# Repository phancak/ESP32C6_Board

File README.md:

# ESP32-C6 Expansion Board

## Overview

This project features a modular expansion board based on the **ESP32-C6** microcontroller, designed to showcase advanced wireless connectivity and interface flexibility for proof-of-concept embedded systems. The board includes **Wi-Fi 6**, **Bluetooth 5**, and **802.15.4 (Thread/Zigbee)** support, making it suitable for modern IoT applications. In addition to its wireless capabilities, the board exposes key communication interfaces like **QSPI**, **SPI**, **I2C**, and **UART**, enabling it to serve as a powerful, plug-and-play module in larger prototype systems.

## Features

- **ESP32-C6 MCU** – RISC-V single-core processor with Wi-Fi 6, BLE 5, Thread, and Zigbee support
- **QSPI Interface** – For high-speed flash memory or display integration
- **SPI, I2C, UART** – Standard communication protocols for versatile interfacing
- **Low Power Operation** – Ideal for battery-powered and energy-conscious applications
- **Modular Design** – Created for reuse across multiple proof-of-concept hardware projects

## Applications

- **IoT Prototyping** – Wireless communication for smart sensors and devices
- **Home Automation** – Thread/Zigbee-enabled devices with cloud connectivity
- **Industrial Monitoring** – Robust wireless links in noisy environments
- **Education & Research** – Hands-on embedded systems development

## Getting Started

### Hardware Requirements

- ESP32-C6 Expansion Board
- Host MCU or baseboard (if applicable)
- USB-C or serial programmer (if needed)
- 3.3V power supply

### Software Requirements

- [ESP-IDF](https://docs.espressif.com/projects/esp-idf/en/latest/esp32c6/index.html) – Espressif's official development framework
- [esptool.py](https://github.com/espressif/esptool) – Flashing utility
- Serial terminal (e.g., `minicom`, `screen`, or [CoolTerm](https://freeware.the-meiers.org/))

## Setup & Usage

1. **Power the Board** – Supply 3.3V through header or onboard regulator.
2. **Connect to PC** – Use a USB-to-serial adapter if required.
3. **Flash Firmware** – Use `esptool.py` or ESP-IDF to upload your application.
4. **Interface with Peripherals** – Connect SPI/I2C/UART/QSPI devices as needed.
5. **Run Application** – Test wireless or peripheral functionality in your project.

## Schematic

You can view the schematic [here](ESP32C6_Board_Schematics.pdf).

## Future Enhancements

- 🔹 **Thread/Zigbee Demos** – Example apps using 802.15.4 stack
- 🔹 **External Flash/Display Support** – Over QSPI
- 🔹 **Power Optimization Modes** – Advanced sleep and wake-up configurations
- 🔹 **Plug-in Board Compatibility** – For stacking with other expansions

## License

This project is open-source under the **MIT License**.

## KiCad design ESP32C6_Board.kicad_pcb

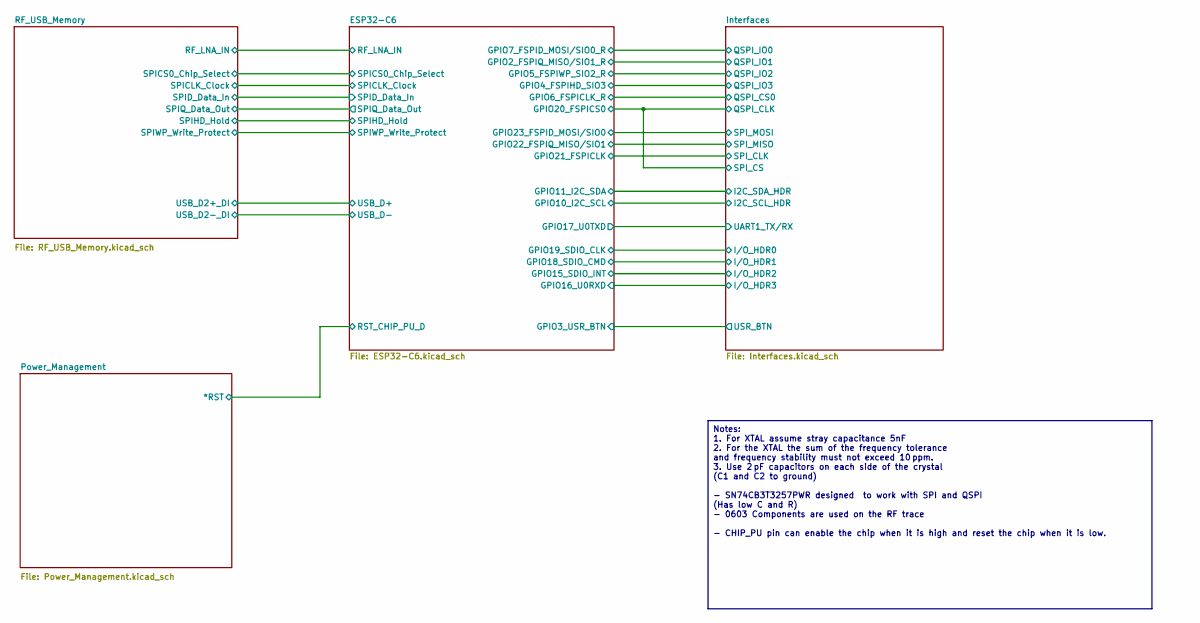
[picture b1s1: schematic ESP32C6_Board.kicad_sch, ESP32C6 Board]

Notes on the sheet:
Notes: 1. For XTAL assume stray capacitance 5nF 2. For the XTAL the sum of the frequency tolerance and frequency stability must not exceed 10 ppm. 3. Use 2 pF capacitors on each side of the crystal (C1 and C2 to ground) - SN74CB3T3257PWR designed to work with SPI and QSPI (Has low C and R) - 0603 C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

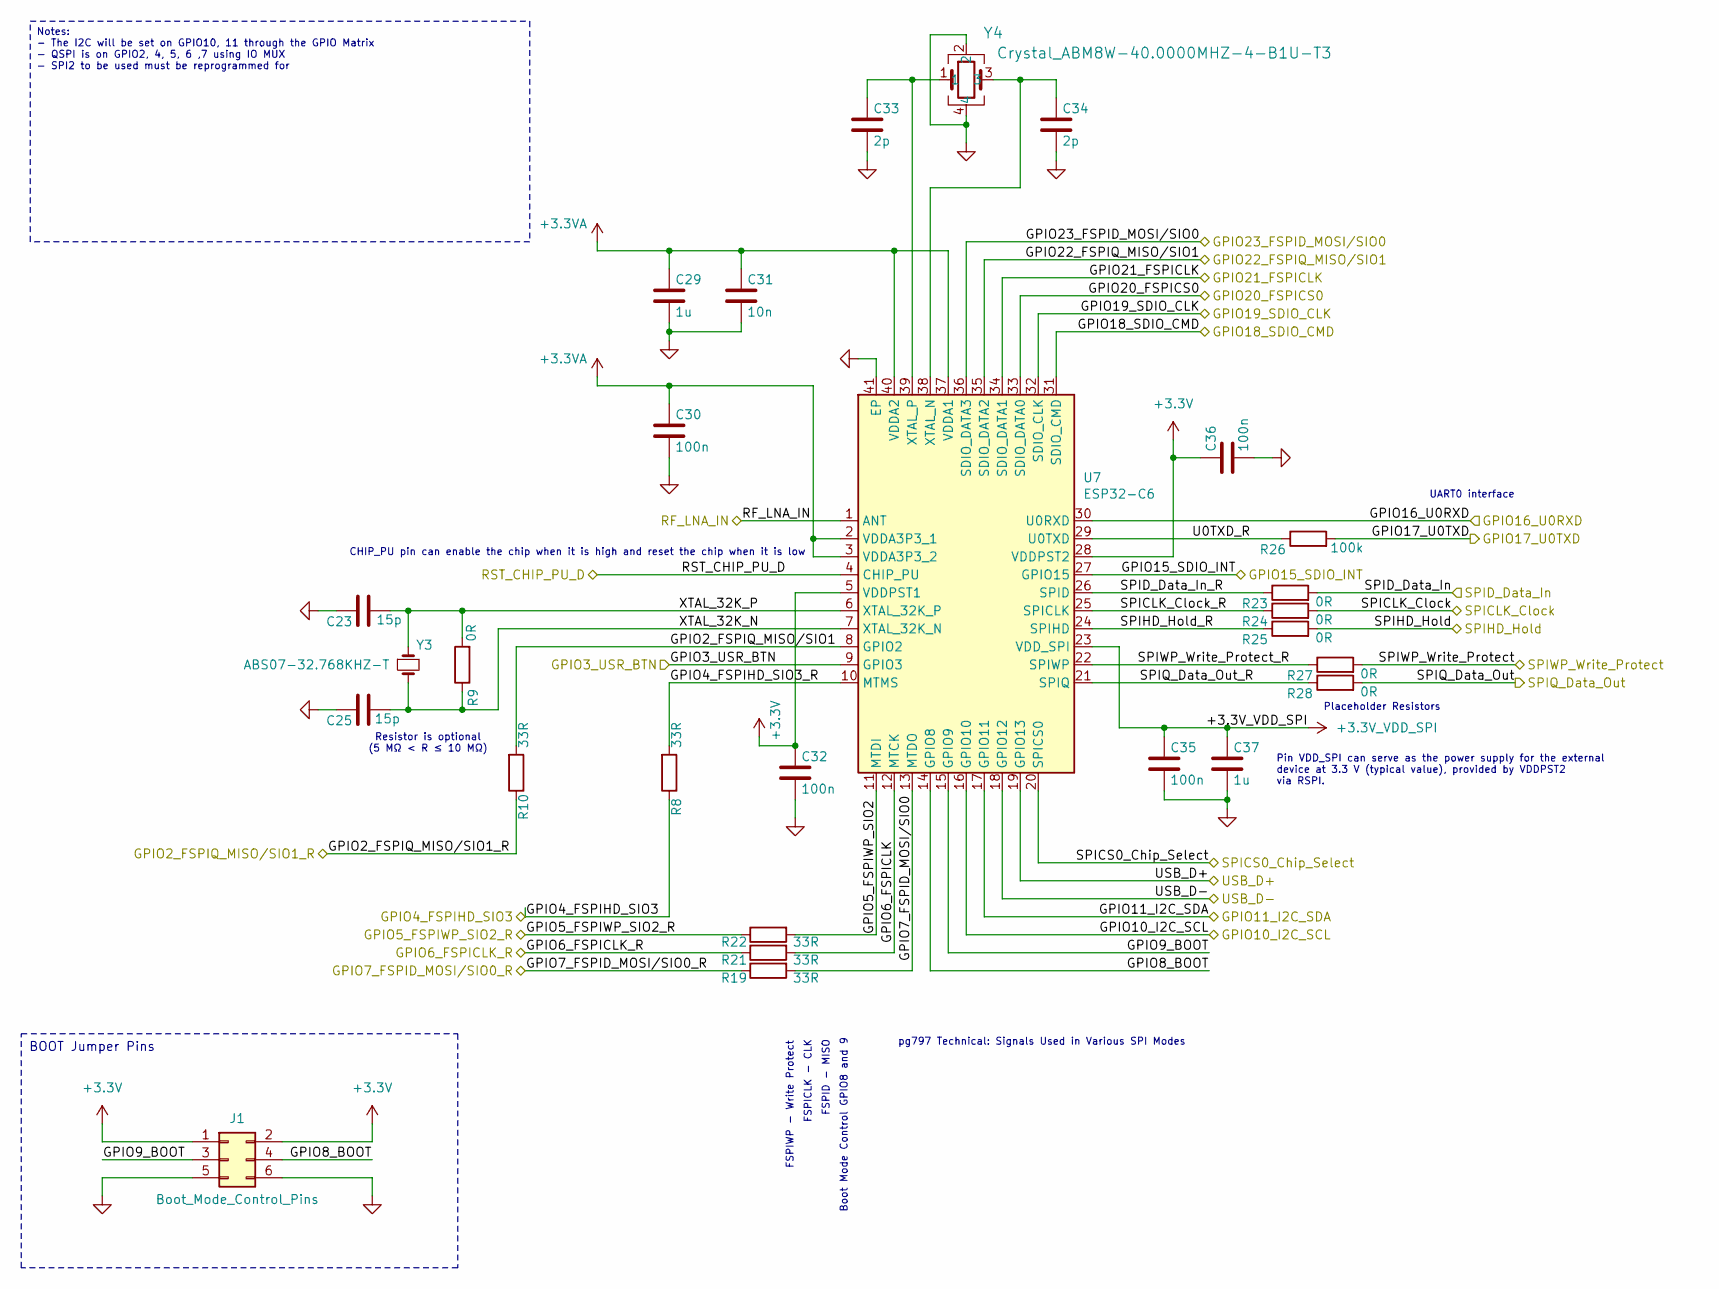
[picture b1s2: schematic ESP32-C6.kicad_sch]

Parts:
C23, C25: 15p; C_0805_2012Metric
C29, C37: 1u; C_0805_2012Metric
C30, C32, C35, C36: 100n; C_0805_2012Metric
C31: 10n; C_0805_2012Metric
C33, C34: 2p; C_0805_2012Metric
J1: Boot_Mode_Control_Pins; PinHeader_2x03_P2.54mm_Vertical
R8, R10, R19, R21, R22: 33R; R_0805_2012Metric
R9, R23, R24, R25, R27, R28: 0R; R_0805_2012Metric
R26: 100k; R_0805_2012Metric
U7: ESP32-C6; ESP32C6_QFN40P500X500X90-41N-D; Mouser Part Number 356-ESP32-C6
Y3: ABS07-32.768KHZ-T; Crystal_ABS07
Y4: Crystal_ABM8W-40.0000MHZ-4-B1U-T3; CRYSTAL4_ABM10W-40.0000MHZ-8-B1U-T3_ABR

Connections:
+3.3V: C32.1, C36.1, J1.1, J1.2, U7.5 (VDDPST1), U7.28 (VDDPST2); also elsewhere on the board
+3.3VA: C29.1, C30.1, C31.1, U7.2 (VDDA3P3_1), U7.3 (VDDA3P3_2), U7.37 (VDDA1), U7.40 (VDDA2); also elsewhere on the board
+3.3V_VDD_SPI: C35.1, C37.1, U7.23 (VDD_SPI); also elsewhere on the board
/ESP32-C6/GPIO2_FSPIQ_MISO/SIO1: R10.2, U7.8 (GPIO2)
/ESP32-C6/GPIO2_FSPIQ_MISO/SIO1_R: R10.1; also elsewhere on the board
/ESP32-C6/GPIO3_USR_BTN: U7.9 (GPIO3); also elsewhere on the board
/ESP32-C6/GPIO4_FSPIHD_SIO3: R8.1; also elsewhere on the board
/ESP32-C6/GPIO4_FSPIHD_SIO3_R: R8.2, U7.10 (MTMS)
/ESP32-C6/GPIO5_FSPIWP_SIO2: R22.2, U7.11 (MTDI)
/ESP32-C6/GPIO5_FSPIWP_SIO2_R: R22.1; also elsewhere on the board
/ESP32-C6/GPIO6_FSPICLK: R21.2, U7.12 (MTCK)
/ESP32-C6/GPIO6_FSPICLK_R: R21.1; also elsewhere on the board
/ESP32-C6/GPIO7_FSPID_MOSI/SIO0: R19.2, U7.13 (MTDO)
/ESP32-C6/GPIO7_FSPID_MOSI/SIO0_R: R19.1; also elsewhere on the board
/ESP32-C6/GPIO8_BOOT: J1.4, U7.14 (GPIO8)
/ESP32-C6/GPIO9_BOOT: J1.3, U7.15 (GPIO9)
/ESP32-C6/GPIO10_I2C_SCL: U7.16 (GPIO10); also elsewhere on the board
/ESP32-C6/GPIO11_I2C_SDA: U7.17 (GPIO11); also elsewhere on the board
/ESP32-C6/GPIO15_SDIO_INT: U7.27 (GPIO15); also elsewhere on the board
/ESP32-C6/GPIO16_U0RXD: U7.30 (U0RXD); also elsewhere on the board
/ESP32-C6/GPIO17_U0TXD: R26.2; also elsewhere on the board
/ESP32-C6/GPIO18_SDIO_CMD: U7.31 (SDIO_CMD); also elsewhere on the board
/ESP32-C6/GPIO19_SDIO_CLK: U7.32 (SDIO_CLK); also elsewhere on the board
/ESP32-C6/GPIO20_FSPICS0: U7.33 (SDIO_DATA0); also elsewhere on the board
/ESP32-C6/GPIO21_FSPICLK: U7.34 (SDIO_DATA1); also elsewhere on the board
/ESP32-C6/GPIO22_FSPIQ_MISO/SIO1: U7.35 (SDIO_DATA2); also elsewhere on the board
/ESP32-C6/GPIO23_FSPID_MOSI/SIO0: U7.36 (SDIO_DATA3); also elsewhere on the board
/ESP32-C6/RF_LNA_IN: U7.1 (ANT); also elsewhere on the board
/ESP32-C6/RST_CHIP_PU_D: U7.4 (CHIP_PU); also elsewhere on the board
/ESP32-C6/SPICLK_Clock: R24.2; also elsewhere on the board
/ESP32-C6/SPICLK_Clock_R: R24.1, U7.25 (SPICLK)
/ESP32-C6/SPICS0_Chip_Select: U7.20 (SPICS0); also elsewhere on the board
/ESP32-C6/SPID_Data_In: R23.2; also elsewhere on the board
/ESP32-C6/SPID_Data_In_R: R23.1, U7.26 (SPID)
/ESP32-C6/SPIHD_Hold: R25.2; also elsewhere on the board
/ESP32-C6/SPIHD_Hold_R: R25.1, U7.24 (SPIHD)
/ESP32-C6/SPIQ_Data_Out: R28.2; also elsewhere on the board
/ESP32-C6/SPIQ_Data_Out_R: R28.1, U7.21 (SPIQ)
/ESP32-C6/SPIWP_Write_Protect: R27.2; also elsewhere on the board
/ESP32-C6/SPIWP_Write_Protect_R: R27.1, U7.22 (SPIWP)
/ESP32-C6/U0TXD_R: R26.1, U7.29 (U0TXD)
/ESP32-C6/USB_D+: U7.19 (GPIO13); also elsewhere on the board
/ESP32-C6/USB_D-: U7.18 (GPIO12); also elsewhere on the board
/ESP32-C6/XTAL_32K_N: C25.1, R9.1, U7.7 (XTAL_32K_N), Y3.2
/ESP32-C6/XTAL_32K_P: C23.1, R9.2, U7.6 (XTAL_32K_P), Y3.1
GND: C23.2, C25.2, C29.2, C30.2, C31.2, C32.2, C33.2, C34.2, C35.2, C36.2, C37.2, J1.5, J1.6, U7.41 (EP), Y4.2, Y4.4; also elsewhere on the board
unnamed: C34.1, U7.38 (XTAL_N), Y4.3
unnamed: C33.1, U7.39 (XTAL_P), Y4.1

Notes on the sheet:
BOOT Jumper Pins
Notes: - The I2C will be set on GPIO10, 11 through the GPIO Matrix - QSPI is on GPIO2, 4, 5, 6 ,7 using IO MUX - SPI2 to be used must be reprogrammed for
Resistor is optional (5 MΩ < R ≤ 10 MΩ)
FSPIWP - Write Protect
FSPID - MISO
FSPICLK - CLK
UART0 interface
Placeholder Resistors
Boot Mode Control GPIO8 and 9
Pin VDD_SPI can serve as the power supply for the external device at 3.3 V (typical value), provided by VDDPST2 via RSPI.
CHIP_PU pin can enable the chip when it is high and reset the chip when it is low
pg797 Technical: Signals Used in Various SPI Modes

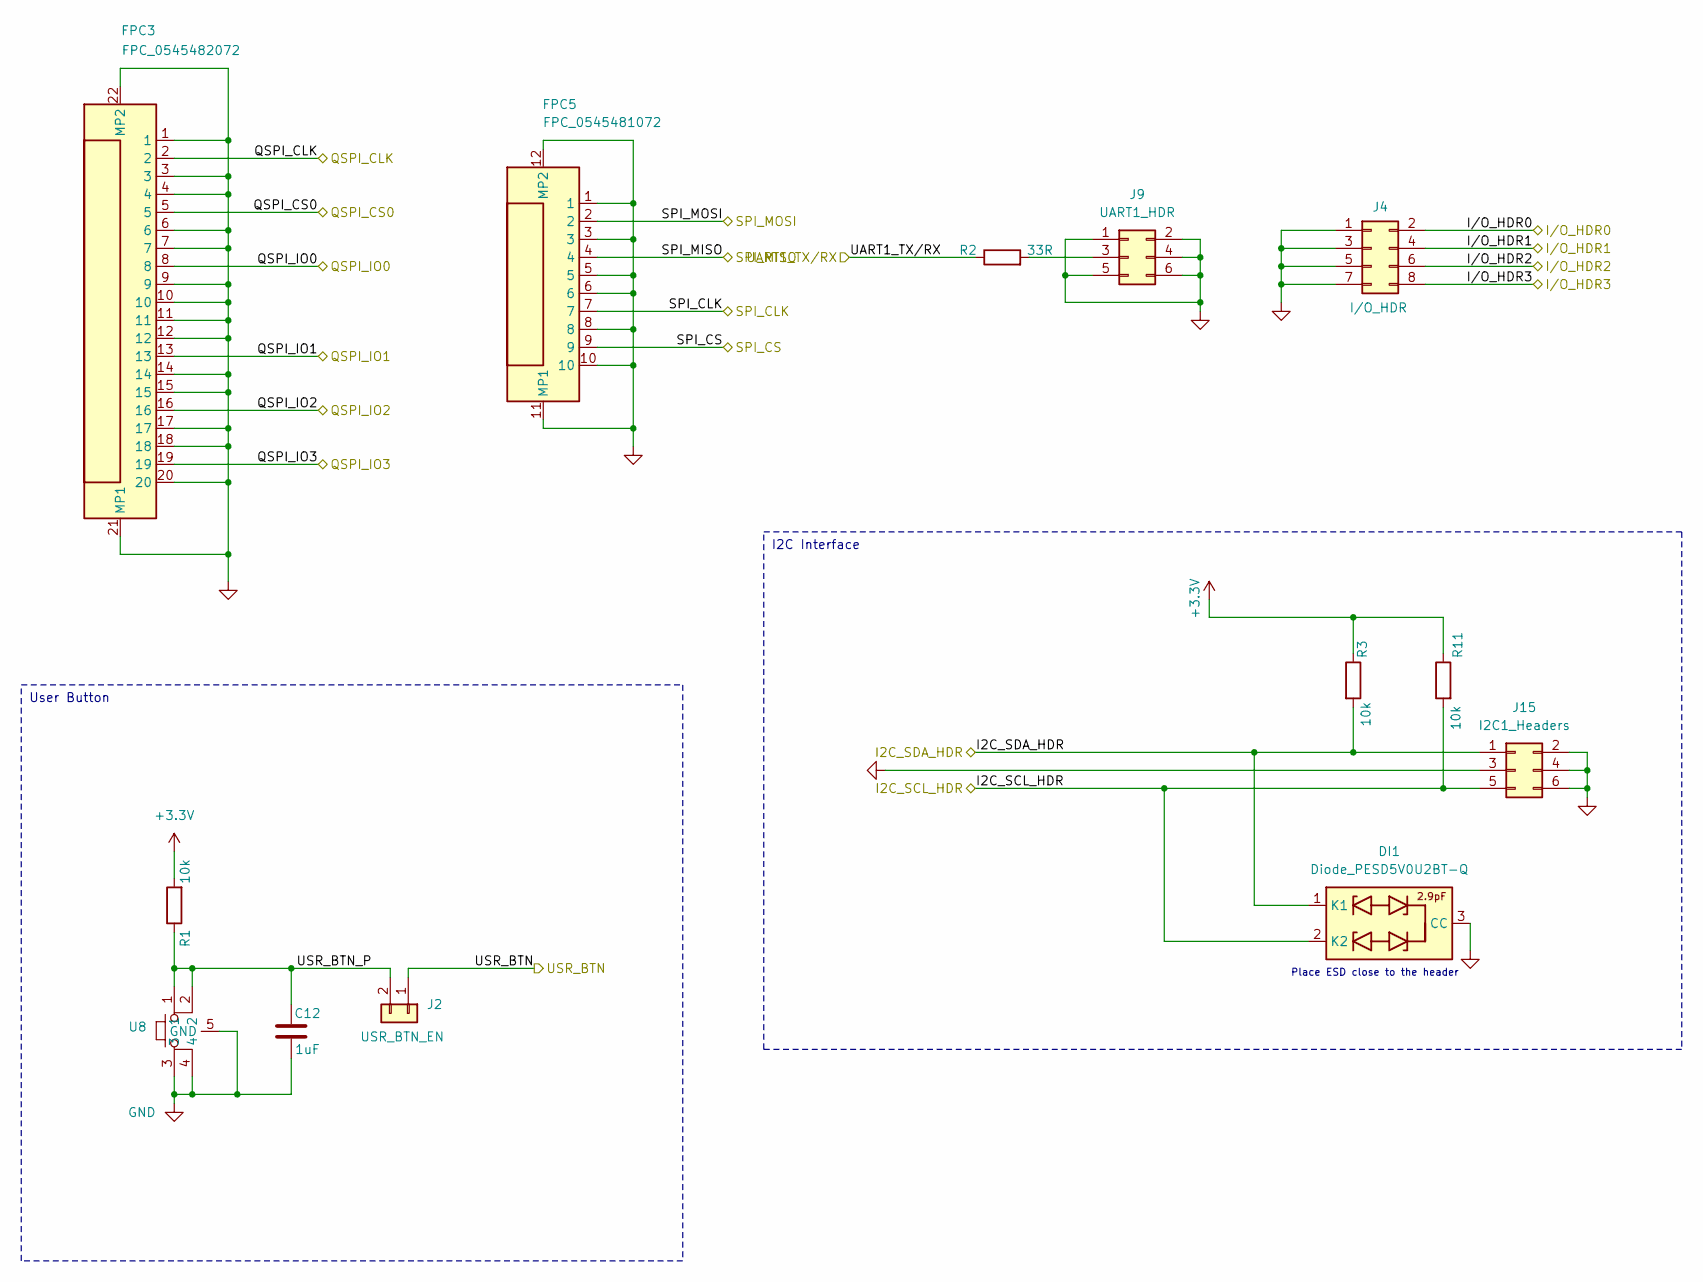
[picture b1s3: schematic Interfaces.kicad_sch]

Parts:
C12: 1uF; C_0805_2012Metric
DI1: Diode_PESD5V0U2BT-Q; SOT-23; Manufacturer_Part_Number BZX84C6V2-7-F; Mouser Part Number 621-BZX84C6V2-F
FPC3: FPC_0545482072; Manufacturer_Part_Number 0545481072
FPC5: FPC_0545481072; Manufacturer_Part_Number 0545481072
J2: USR_BTN_EN; PinHeader_1x02_P2.54mm_Vertical
J4: I/O_HDR; PinHeader_2x04_P2.54mm_Horizontal
J9: UART1_HDR; PinHeader_2x03_P2.54mm_Horizontal_Court
J15: I2C1_Headers; PinHeader_2x03_P2.54mm_Horizontal_Court
R1, R3, R11: 10k; R_0805_2012Metric
R2: 33R; R_0805_2012Metric
U8: Button_KMR231GLFS

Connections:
+3.3V: R1.2, R3.1, R11.1; also elsewhere on the board
/ESP32-C6/GPIO2_FSPIQ_MISO/SIO1_R: FPC3.13; also elsewhere on the board
/ESP32-C6/GPIO3_USR_BTN: J2.1; also elsewhere on the board
/ESP32-C6/GPIO4_FSPIHD_SIO3: FPC3.19; also elsewhere on the board
/ESP32-C6/GPIO5_FSPIWP_SIO2_R: FPC3.16; also elsewhere on the board
/ESP32-C6/GPIO6_FSPICLK_R: FPC3.5; also elsewhere on the board
/ESP32-C6/GPIO7_FSPID_MOSI/SIO0_R: FPC3.8; also elsewhere on the board
/ESP32-C6/GPIO10_I2C_SCL: DI1.2 (K2), J15.5, R11.2; also elsewhere on the board
/ESP32-C6/GPIO11_I2C_SDA: DI1.1 (K1), J15.1, R3.2; also elsewhere on the board
/ESP32-C6/GPIO15_SDIO_INT: J4.6; also elsewhere on the board
/ESP32-C6/GPIO16_U0RXD: J4.8; also elsewhere on the board
/ESP32-C6/GPIO17_U0TXD: R2.1; also elsewhere on the board
/ESP32-C6/GPIO18_SDIO_CMD: J4.4; also elsewhere on the board
/ESP32-C6/GPIO19_SDIO_CLK: J4.2; also elsewhere on the board
/ESP32-C6/GPIO20_FSPICS0: FPC3.2, FPC5.9; also elsewhere on the board
/ESP32-C6/GPIO21_FSPICLK: FPC5.7; also elsewhere on the board
/ESP32-C6/GPIO22_FSPIQ_MISO/SIO1: FPC5.4; also elsewhere on the board
/ESP32-C6/GPIO23_FSPID_MOSI/SIO0: FPC5.2; also elsewhere on the board
/Interfaces/USR_BTN_P: C12.2, J2.2, R1.1, U8.1, U8.2
GND: C12.1, DI1.3 (CC), FPC3.1, FPC3.3, FPC3.4, FPC3.6, FPC3.7, FPC3.9, FPC3.10, FPC3.11, FPC3.12, FPC3.14, FPC3.15, FPC3.17, FPC3.18, FPC3.20, FPC3.21 (MP1), FPC3.22 (MP2), FPC5.1, FPC5.3, FPC5.5, FPC5.6, FPC5.8, FPC5.10, FPC5.11 (MP1), FPC5.12 (MP2), J4.1, J4.3, J4.5, J4.7, J9.1, J9.2, J9.4, J9.5, J9.6, J15.2, J15.3, J15.4, J15.6, U8.3, U8.4, U8.5 (GND); also elsewhere on the board
unnamed: J9.3, R2.2

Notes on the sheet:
User Button
I2C Interface
Place ESD close to the header

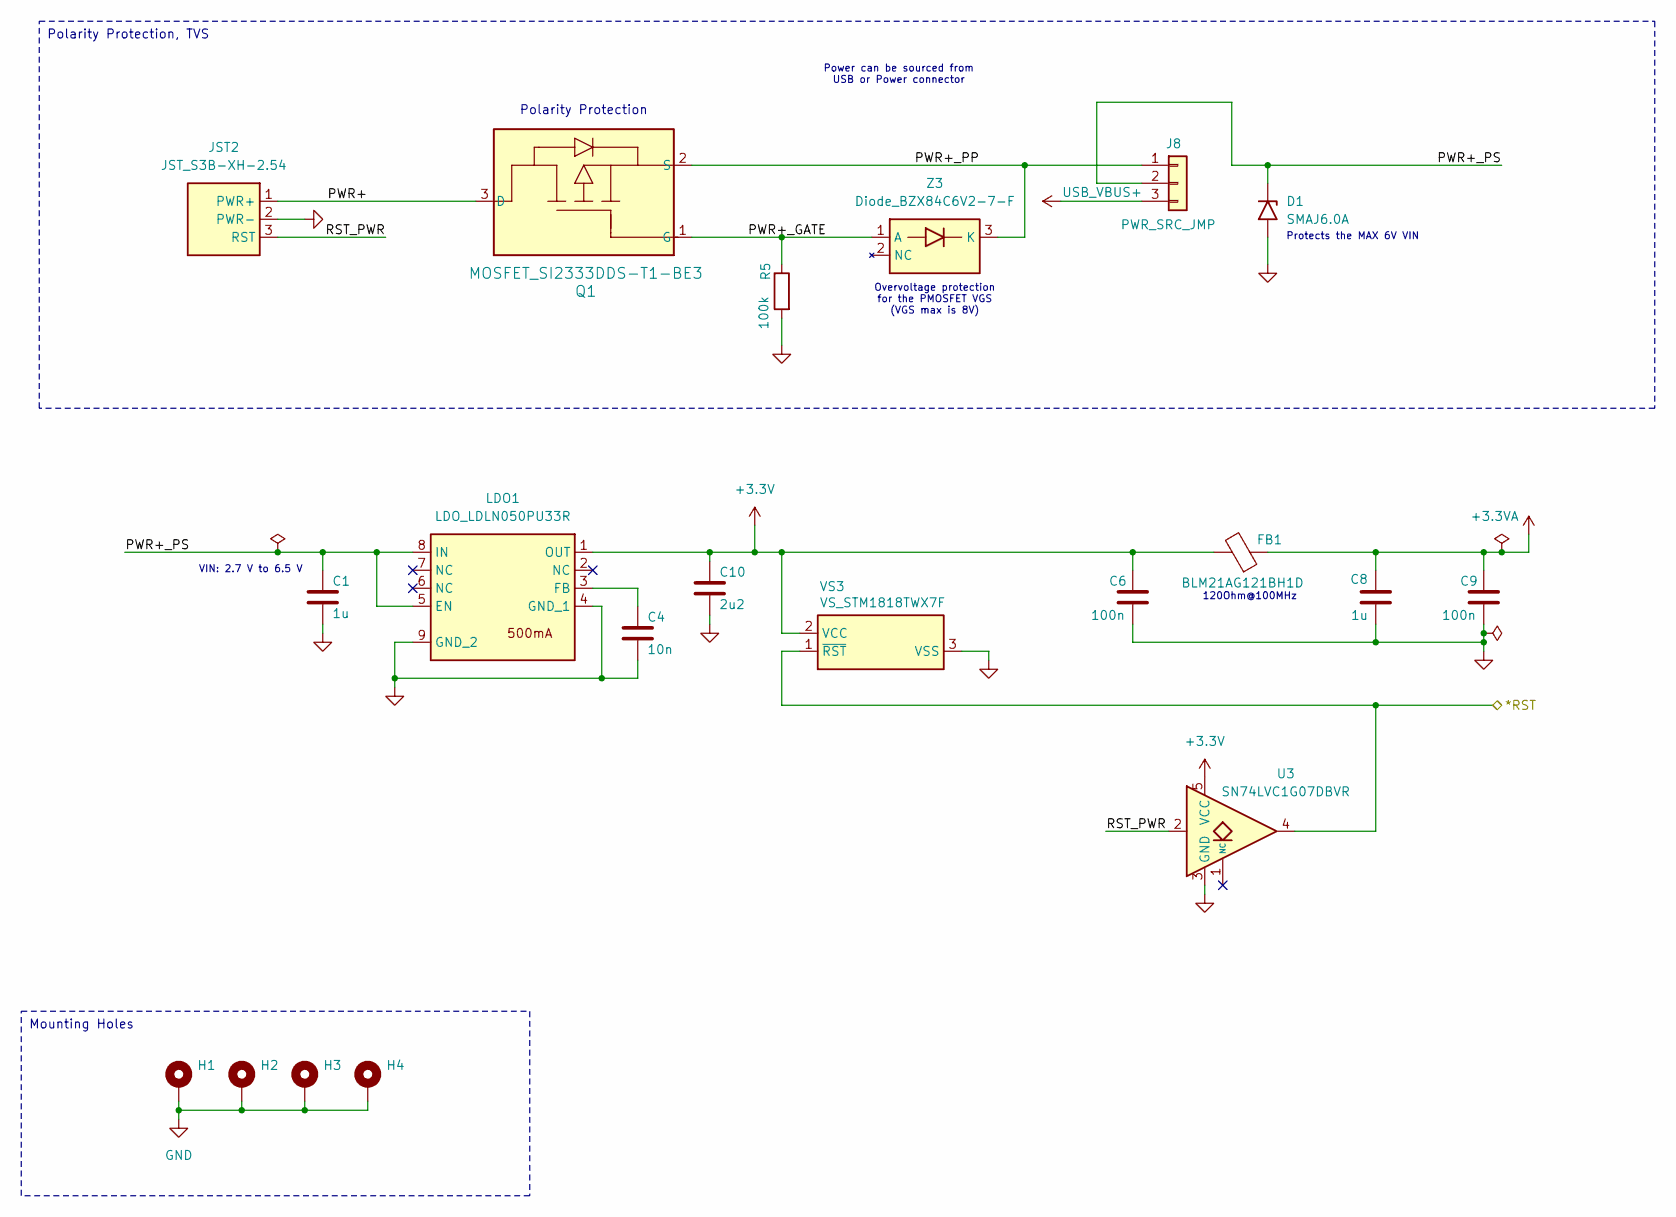
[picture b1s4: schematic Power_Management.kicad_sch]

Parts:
C1, C8: 1u; C_0805_2012Metric
C4: 10n; C_0805_2012Metric
C6, C9: 100n; C_0805_2012Metric
C10: 2u2; C_0805_2012Metric
D1: SMAJ6.0A; DO-214AC-2
FB1: BLM21AG121BH1D; C_0805_2012Metric
H1, H2, H3, H4: MountingHole_Pad; MountingHole_3.2mm_M3_Pad
J8: PWR_SRC_JMP; PinHeader_1x03_P2.54mm_Vertical
JST2: JST_S3B-XH-2.54; JST_S3B-XH-SHDRRA3W64P0X250_1X3_990X1150X610P; Mouser Part Number 306-S3BXHA1LFSN
LDO1: LDO_LDLN050PU33R; DFN-8-1EP_3x3mm_P0.65mm_EP1.7x2.05mm; Manufacturer_Part_Number LD39200DPUR; Mouser Part Number 511-LD39200DPUR
Q1: MOSFET_SI2333DDS-T1-BE3; MOSFET_ SI2333DDS_SOT_DS-T1-BE3_VIS
R5: 100k; R_0805_2012Metric
U3: SN74LVC1G07DBVR; SOT-23-5
VS3: VS_STM1818TWX7F; SOT-23-3_SOT103P237X112-3N; Mouser Part Number 511-STM1813LWX7F
Z3: Diode_BZX84C6V2-7-F; Diode_BZX84C6V2_SOT96P240X110-3N; Manufacturer_Part_Number BZX84C6V2-7-F; Mouser Part Number 621-BZX84C6V2-F

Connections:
+3.3V: C6.1, C10.1, FB1.2, LDO1.1 (OUT), U3.5 (VCC), VS3.2 (VCC); also elsewhere on the board
+3.3VA: C8.1, C9.1, FB1.1; also elsewhere on the board
/ESP32-C6/RST_CHIP_PU_D: U3.4, VS3.1 (~RST); also elsewhere on the board
/Power_Management/PWR+: JST2.1 (PWR+), Q1.3 (D)
/Power_Management/PWR+_GATE: Q1.1 (G), R5.1, Z3.1 (A)
/Power_Management/PWR+_PP: J8.1, Q1.2 (S), Z3.3 (K)
/Power_Management/PWR+_PS: C1.1, D1.1 (K), J8.2, LDO1.5 (EN), LDO1.8 (IN)
/Power_Management/RST_PWR: JST2.3 (RST), U3.2
GND: C1.2, C4.2, C6.2, C8.2, C9.2, C10.2, D1.2 (A), H1.1, H2.1, H3.1, H4.1, JST2.2 (PWR-), LDO1.4 (GND_1), LDO1.9 (GND_2), R5.2, U3.3 (GND), VS3.3 (VSS); also elsewhere on the board
unnamed: C4.1, LDO1.3 (FB)
USB_VBUS+: J8.3; also elsewhere on the board

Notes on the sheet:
Mounting Holes
Polarity Protection, TVS
Power can be sourced from USB or Power connector
120Ohm@100MHz
VIN: 2.7 V to 6.5 V
Overvoltage protection for the PMOSFET VGS (VGS max is 8V)
Protects the MAX 6V VIN
Polarity Protection

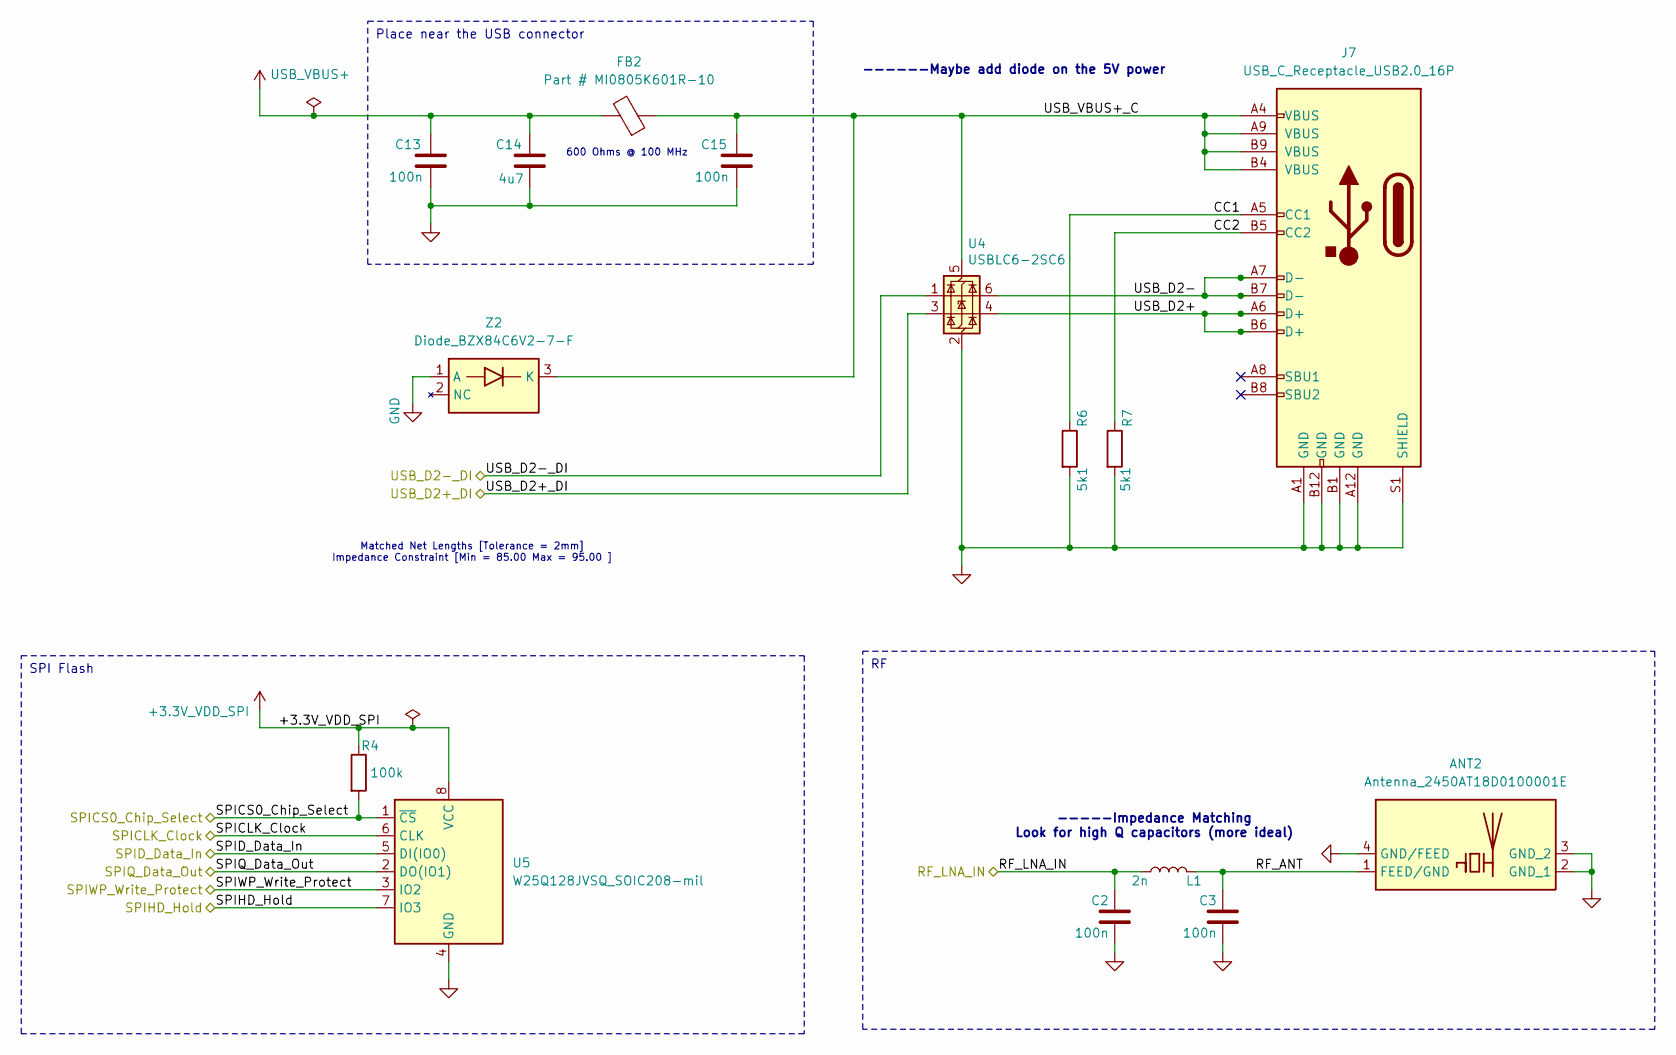
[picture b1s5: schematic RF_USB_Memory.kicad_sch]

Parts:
ANT2: Antenna_2450AT18D0100001E; Mouser Part Number 609-2450AT18D0100001
C2, C3: 100n; C_0603_1608Metric
C13, C15: 100n; C_0805_2012Metric
C14: 4u7; C_0805_2012Metric
FB2: Part # MI0805K601R-10; C_0805_2012Metric
J7: USB_C_Receptacle_USB2.0_16P; USB_C_Receptacle_HRO_TYPE-C-31-M-12
L1: 2n; L_0603_1608Metric
R4: 100k; R_0805_2012Metric
R6, R7: 5k1; R_0805_2012Metric
U4: USBLC6-2SC6; SOT-23-6
U5: W25Q128JVSQ_SOIC208-mil; SOIC-8_5.23x5.23mm_P1.27mm
Z2: Diode_BZX84C6V2-7-F; Diode_BZX84C6V2_SOT96P240X110-3N; Manufacturer_Part_Number BZX84C6V2-7-F; Mouser Part Number 621-BZX84C6V2-F

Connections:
+3.3V_VDD_SPI: R4.1, U5.8 (VCC); also elsewhere on the board
/ESP32-C6/RF_LNA_IN: C2.1, L1.2; also elsewhere on the board
/ESP32-C6/SPICLK_Clock: U5.6 (CLK); also elsewhere on the board
/ESP32-C6/SPICS0_Chip_Select: R4.2, U5.1 (~CS); also elsewhere on the board
/ESP32-C6/SPID_Data_In: U5.5 (DI(IO0)); also elsewhere on the board
/ESP32-C6/SPIHD_Hold: U5.7 (IO3); also elsewhere on the board
/ESP32-C6/SPIQ_Data_Out: U5.2 (DO(IO1)); also elsewhere on the board
/ESP32-C6/SPIWP_Write_Protect: U5.3 (IO2); also elsewhere on the board
/ESP32-C6/USB_D+: U4.3 (I/O2); also elsewhere on the board
/ESP32-C6/USB_D-: U4.1 (I/O1); also elsewhere on the board
/RF_USB_Memory/CC1: J7.A5 (CC1), R6.1
/RF_USB_Memory/CC2: J7.B5 (CC2), R7.1
/RF_USB_Memory/RF_ANT: ANT2.1 (FEED/GND), C3.1, L1.1
/RF_USB_Memory/USB_D2+: J7.A6 (D+), J7.B6 (D+), U4.4 (I/O2)
/RF_USB_Memory/USB_D2-: J7.A7 (D-), J7.B7 (D-), U4.6 (I/O1)
/RF_USB_Memory/USB_VBUS+_C: C15.1, FB2.1, J7.A4 (VBUS), J7.A9 (VBUS), J7.B4 (VBUS), J7.B9 (VBUS), U4.5 (VBUS), Z2.3 (K)
GND: ANT2.2 (GND_1), ANT2.3 (GND_2), ANT2.4 (GND/FEED), C2.2, C3.2, C13.2, C14.2, C15.2, J7.A1 (GND), J7.A12 (GND), J7.B1 (GND), J7.B12 (GND), J7.S1 (SHIELD), R6.2, R7.2, U4.2 (GND), U5.4 (GND), Z2.1 (A); also elsewhere on the board
USB_VBUS+: C13.1, C14.1, FB2.2; also elsewhere on the board

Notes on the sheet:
SPI Flash
Place near the USB connector
Matched Net Lengths [Tolerance = 2mm] Impedance Constraint [Min = 85.00 Max = 95.00 ]
-----Impedance Matching Look for high Q capacitors (more ideal)
------Maybe add diode on the 5V power
600 Ohms @ 100 MHz

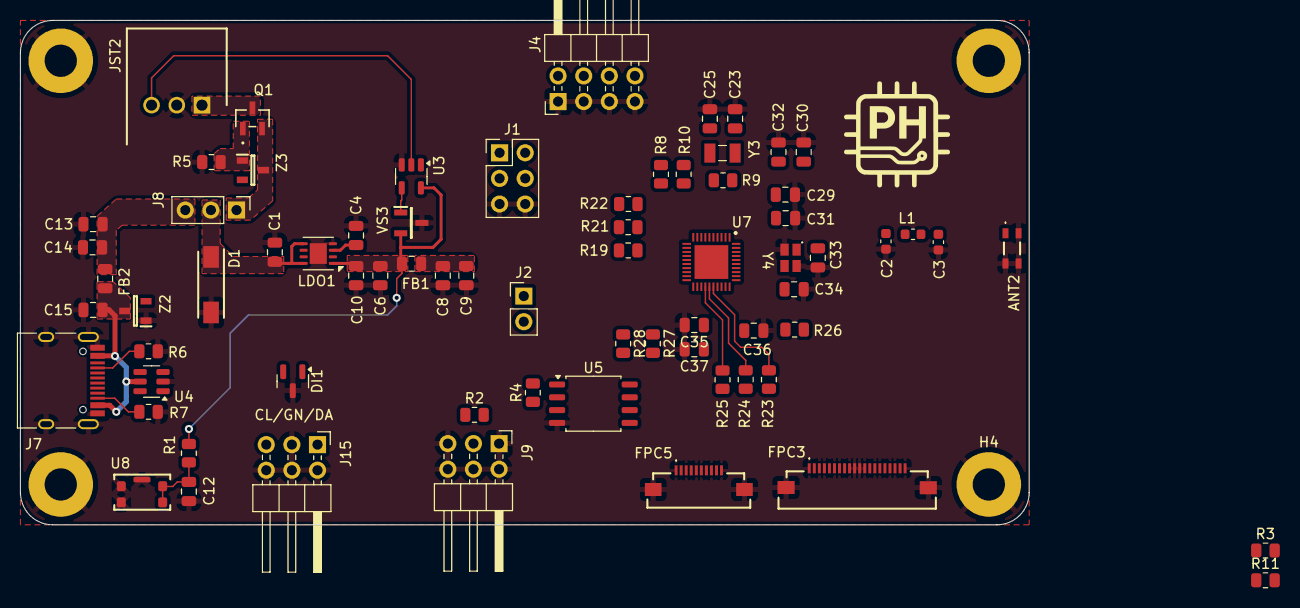
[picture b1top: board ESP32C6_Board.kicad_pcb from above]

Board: 4 copper layers, 100.0 x 50.0 mm, 75 parts (0 on the bottom side), 63 nets.
